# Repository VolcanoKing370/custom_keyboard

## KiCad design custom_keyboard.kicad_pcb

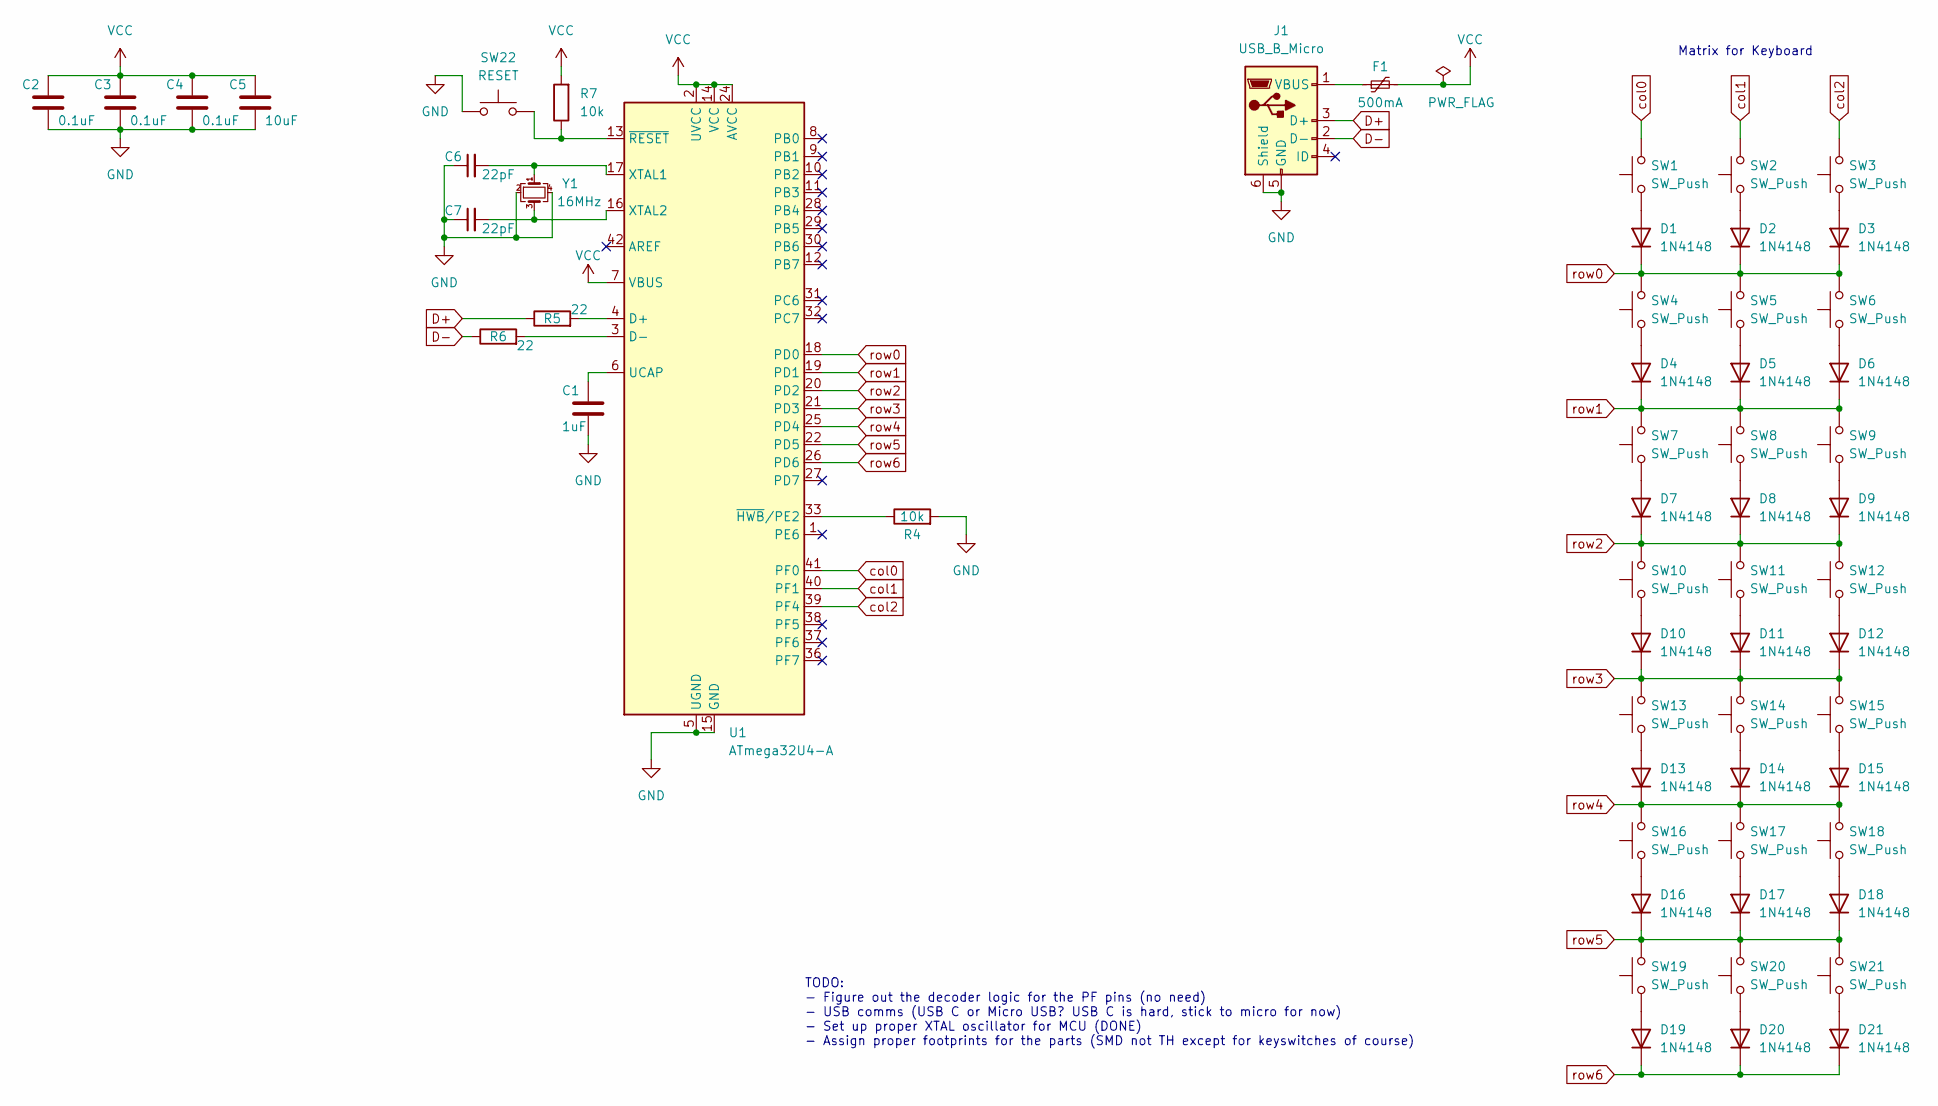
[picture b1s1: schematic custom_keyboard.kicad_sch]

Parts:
C1: 1uF; C_0805_2012Metric_Pad1.18x1.45mm_HandSolder
C2, C3, C4: 0.1uF; C_0805_2012Metric_Pad1.18x1.45mm_HandSolder
C5: 10uF; C_0805_2012Metric_Pad1.18x1.45mm_HandSolder
C6, C7: 22pF; C_0805_2012Metric_Pad1.18x1.45mm_HandSolder
D1, D2, D3, D4, D5, D6, D7, D8, D9, D10, D11, D12, D13, D14, D15, D16, D17, D18, D19, D20, D21: 1N4148; D_SOD-123
F1: 500mA; Fuse_1206_3216Metric_Pad1.42x1.75mm_HandSolder
J1: USB_B_Micro; USB_Micro-B_Molex-105017-0001
R4, R7: 10k; R_0805_2012Metric_Pad1.20x1.40mm_HandSolder
R5, R6: 22; R_0805_2012Metric_Pad1.20x1.40mm_HandSolder
SW1, SW2, SW3, SW4, SW5, SW6, SW7, SW8, SW9, SW10, SW11, SW12, SW13, SW14, SW15, SW16, SW17, SW18, SW19, SW20, SW21: SW_Push; SW_Gateron_LowProfile_THT
SW22: RESET; SW_Push_1P1T_XKB_TS-1187A
U1: ATmega32U4-A; TQFP-44_10x10mm_P0.8mm
Y1: 16MHz; Crystal_SMD_3225-4Pin_3.2x2.5mm_HandSoldering

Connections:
D+: J1.3 (D+), R5.1
D-: J1.2 (D-), R6.1
GND: C1.2, C2.2, C3.2, C4.2, C5.2, C6.1, C7.1, J1.5 (GND), J1.6 (Shield), R4.2, SW22.1, U1.5 (UGND), U1.15 (GND), U1.23 (GND), U1.35 (GND), U1.43 (GND), Y1.2, Y1.4
unnamed: D1.2 (A), SW1.1
unnamed: D2.2 (A), SW2.1
unnamed: D3.2 (A), SW3.1
unnamed: D4.2 (A), SW4.1
unnamed: D5.2 (A), SW5.1
unnamed: D6.2 (A), SW6.1
unnamed: D7.2 (A), SW7.1
unnamed: D8.2 (A), SW8.1
unnamed: D9.2 (A), SW9.1
unnamed: D10.2 (A), SW10.1
unnamed: D11.2 (A), SW11.1
unnamed: D12.2 (A), SW12.1
unnamed: D13.2 (A), SW13.1
unnamed: D14.2 (A), SW14.1
unnamed: D15.2 (A), SW15.1
unnamed: D16.2 (A), SW16.1
unnamed: D17.2 (A), SW17.1
unnamed: D18.2 (A), SW18.1
unnamed: D19.2 (A), SW19.1
unnamed: D20.2 (A), SW20.1
unnamed: D21.2 (A), SW21.1
unnamed: F1.1, J1.1 (VBUS)
unnamed: R5.2, U1.4 (D+)
unnamed: R6.2, U1.3 (D-)
unnamed: C1.1, U1.6 (UCAP)
unnamed: C6.2, U1.17 (XTAL1), Y1.1
unnamed: C7.2, U1.16 (XTAL2), Y1.3
unnamed: R4.1, U1.33 (~HWB/PE2)
unnamed: R7.1, SW22.2, U1.13 (~RESET)
VCC: C2.1, C3.1, C4.1, C5.1, F1.2, R7.2, U1.2 (UVCC), U1.7 (VBUS), U1.14 (VCC), U1.24 (AVCC), U1.34 (VCC), U1.44 (AVCC)
col0: SW1.2, U1.41 (PF0)
col1: SW2.2, U1.40 (PF1)
col2: SW3.2, U1.39 (PF4)
row0: D1.1 (K), D2.1 (K), D3.1 (K), SW4.2, SW5.2, SW6.2, U1.18 (PD0)
row1: D4.1 (K), D5.1 (K), D6.1 (K), SW7.2, SW8.2, SW9.2, U1.19 (PD1)
row2: D7.1 (K), D8.1 (K), D9.1 (K), SW10.2, SW11.2, SW12.2, U1.20 (PD2)
row3: D10.1 (K), D11.1 (K), D12.1 (K), SW13.2, SW14.2, SW15.2, U1.21 (PD3)
row4: D13.1 (K), D14.1 (K), D15.1 (K), SW16.2, SW17.2, SW18.2, U1.25 (PD4)
row5: D16.1 (K), D17.1 (K), D18.1 (K), SW19.2, SW20.2, SW21.2, U1.22 (PD5)
row6: D19.1 (K), D20.1 (K), D21.1 (K), U1.26 (PD6)

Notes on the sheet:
TODO: - Figure out the decoder logic for the PF pins (no need) - USB comms (USB C or Micro USB? USB C is hard, stick to micro for now) - Set up proper XTAL oscillator for MCU (DONE) - Assign proper footprints for the parts (SMD not TH except for keyswitches of course)
Matrix for Keyboard

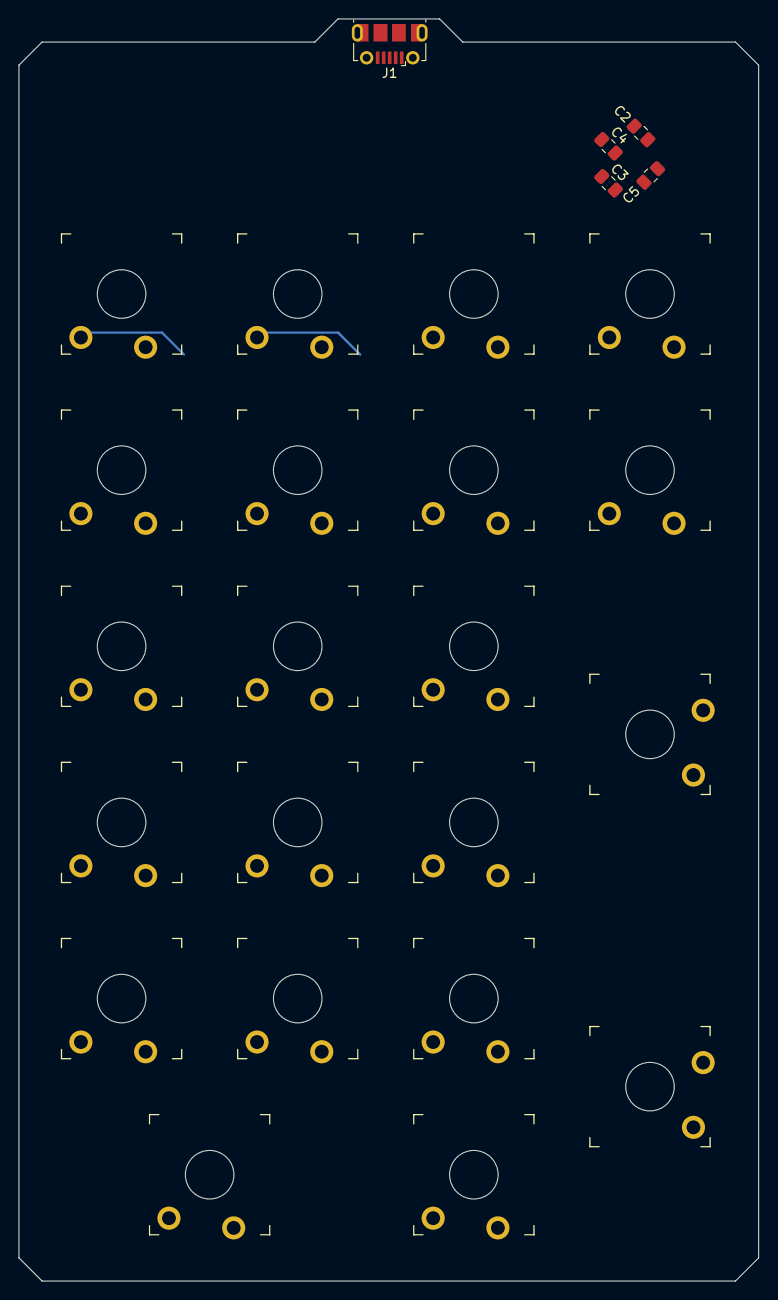
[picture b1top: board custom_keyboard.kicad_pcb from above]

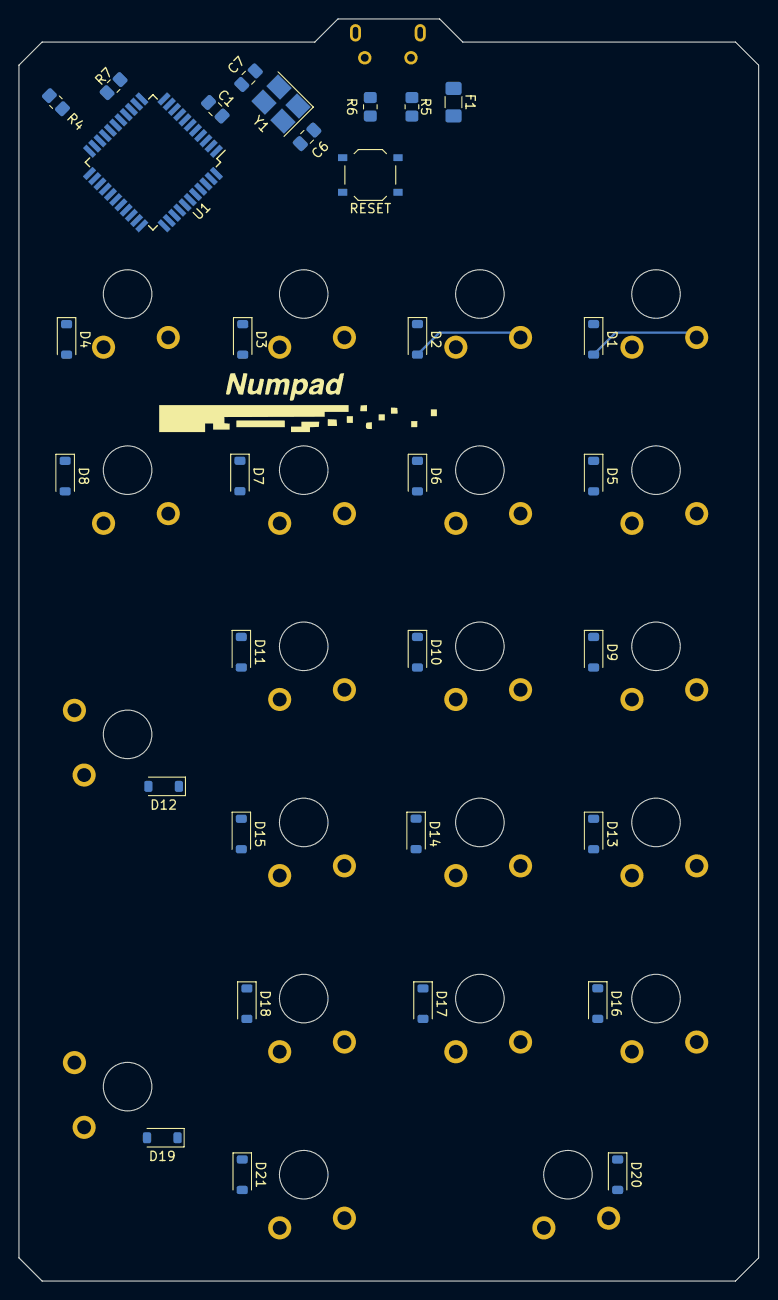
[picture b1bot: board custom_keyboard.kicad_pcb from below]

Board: 2 copper layers, 80.0 x 136.5 mm, 59 parts (33 on the bottom side), 42 nets.

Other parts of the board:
G1: LOGO
